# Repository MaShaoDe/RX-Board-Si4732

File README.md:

# RX-Board Si4732

Steckbare Empfänger-Baugruppe für das [Funkfüürli](https://github.com/MaShaoDe/Funkfuerli), das Notfallradio zum Selberbauen für Kinder und Schüler.

Das RX-Board trägt den Empfängerchip Si4732-A10 (UKW, MW, KW, LW, RDS) mit Quarz und Beschaltung. Es wird komplett bestückt bestellt. Die Kinder löten nur die Stiftleisten.

**Stand:** Rev A ist bestellt, gefertigt und unterwegs. Die Tests folgen nach Lieferung (siehe [docs/labortest.md](docs/labortest.md)). Bekannte Fehler auf Rev A werden in Rev B korrigiert.

* Beschreibung, Pinbelegung und Anforderungen: [docs/rx-board.md](docs/rx-board.md)
* Englische Kurzfassung: [README.en.md](README.en.md)
* Lizenzen: [LICENSE.md](LICENSE.md)

## Ordner

| Ordner | Inhalt |
|---|---|
| `docs/` | Beschreibung, Anforderungen, Prüfanleitung |
| `hardware/` | KiCad Projekt, Fertigungsdaten Rev A (Stückliste, Bestückungsliste) |
| `LICENSES/` | Lizenztexte |

## Plan

1. Erledigt: Schaltplan, Layout und Fertigungsdaten Rev A, Fertigung bei JLCPCB.
2. Offen: Test Rev A (Testprogramm liest Chip aus und stimmt einen Sender ab).
3. Offen: Fehler von Rev A sammeln, Layout Rev B.

Copyright 2026 FerienBSD aka Marcel Sauder. Hardware CERN-OHL-P-2.0, Doku CC-BY-4.0.

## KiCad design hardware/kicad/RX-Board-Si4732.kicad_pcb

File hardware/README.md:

# hardware

Rev A des RX-Boards (UKW, MW, LW). Stand 2026-11-19: **gefertigt, Lieferung und Tests stehen aus.** Entwurfsstand vom 2026-11-15: ERC in KiCad 10: 0 Meldungen. DRC Durchgang 2: 0 Fehler. Die Footprints stammen jetzt aus der echten KiCad-Bibliothek (`tools/fplib.json`). Noch offen: DRC der neuen Version, Antennenpfade im Labortest, JLCPCB-Vorschau.

## Inhalt

| Pfad | Inhalt |
|---|---|
| `kicad/RX-Board-Si4732.kicad_pro` | KiCad-Projekt (erzeugt im KiCad-8-Format, in KiCad 10 geladen und gespeichert) |
| `kicad/RX-Board-Si4732.kicad_sch` | Schaltplan. Verbindungen laufen über gleichnamige Netzbezeichner, nicht über gezeichnete Leitungen |
| `kicad/RX-Board-Si4732.kicad_pcb` | Platine 44 x 30 mm, 2 Lagen, bestückt und verlegt, Masseflächen vorne und hinten |
| `bom/RX-Board_RevA_BOM.csv` | Stückliste des Entwurfs. Die Stückliste mit LCSC-Nummern liegt in `production/` |
| `production/` | Fertigungsdaten Rev A (Stückliste mit LCSC-Nummern, Bestückungsdatei), siehe `production/README.md` |
| `preview/layout-vorschau.png` | Grobe Vorschau des Layouts (kein KiCad-Bild) |
| `tools/` | Python-Skripte, die diese Dateien erzeugen (siehe unten). `fplib.json` enthält die Footprints aus der KiCad-Bibliothek |

## Erste Schritte in KiCad

1. Projekt öffnen. Wenn KiCad nach Symbol- oder Footprint-Bibliotheken fragt, "Aktuelle Einstellungen behalten" wählen. Die Symbole sind im Schaltplan eingebettet.
2. Schaltplan: ERC ausführen. Zu erwarten sind Warnungen zu Power-Pins ohne Treiber (alle Pins sind als passiv gesetzt) und "Pin nicht auf Raster".
3. Platine: Zonen füllen (Taste B), dann DRC ausführen. Zu prüfen: Abstände, Silkscreen über Pads, Textgrössen, Beschriftung auf der Rückseite (gespiegelt).
4. Footprints mit "Aktualisieren aus Schaltplan" gegen die Standardbibliothek abgleichen.
5. Layout durchsehen. Das Verlegen hat ein Skript gemacht (Gitter-Router). Kritisch sind die Antennenpfade (FM, AM), der Quarz und die Lage der Teile zum Ferritstab.
6. Gerber, Bohrdateien und Bestückungsdatei (Position) in KiCad exportieren, im JLCPCB-Viewer Drehung der Bauteile prüfen.

## Erzeugen

```
cd hardware/tools
python3 rxwrite.py      # schreibt kicad/ und bom/
python3 fpextract.py <von KiCad gespeicherte .kicad_pcb>   # nur nötig, um fplib.json aus der Bibliothek zu erneuern
python3 rxcheck.py      # Abstands- und Verbindungsprüfung
python3 rxsyntax.py ../kicad/RX-Board-Si4732.kicad_pcb ../kicad/RX-Board-Si4732.kicad_sch
```

Benötigt Python 3 und numpy. `rxmodel.py` enthält Bauteile, Netze und Platzierung. Änderungen dort ergeben nach `rxwrite.py` neue Dateien. Manuelle Änderungen in KiCad werden dabei überschrieben.

## Offen

* Quarz: Bauform 3215, Lastkapazität 12.5 pF, Toleranz laut AN383 ±50 ppm. Der bestellte Typ (LCSC C32346) ist gegen diese Werte zu prüfen.
* FM-Spule 56 nH ist ein Startwert aus AN383 und wird im Labortest geprüft (Mikroe nutzt 270 nH).
* Footprint der Stiftleiste, Kodierung und mechanische Lage zur Hauptplatine festlegen.

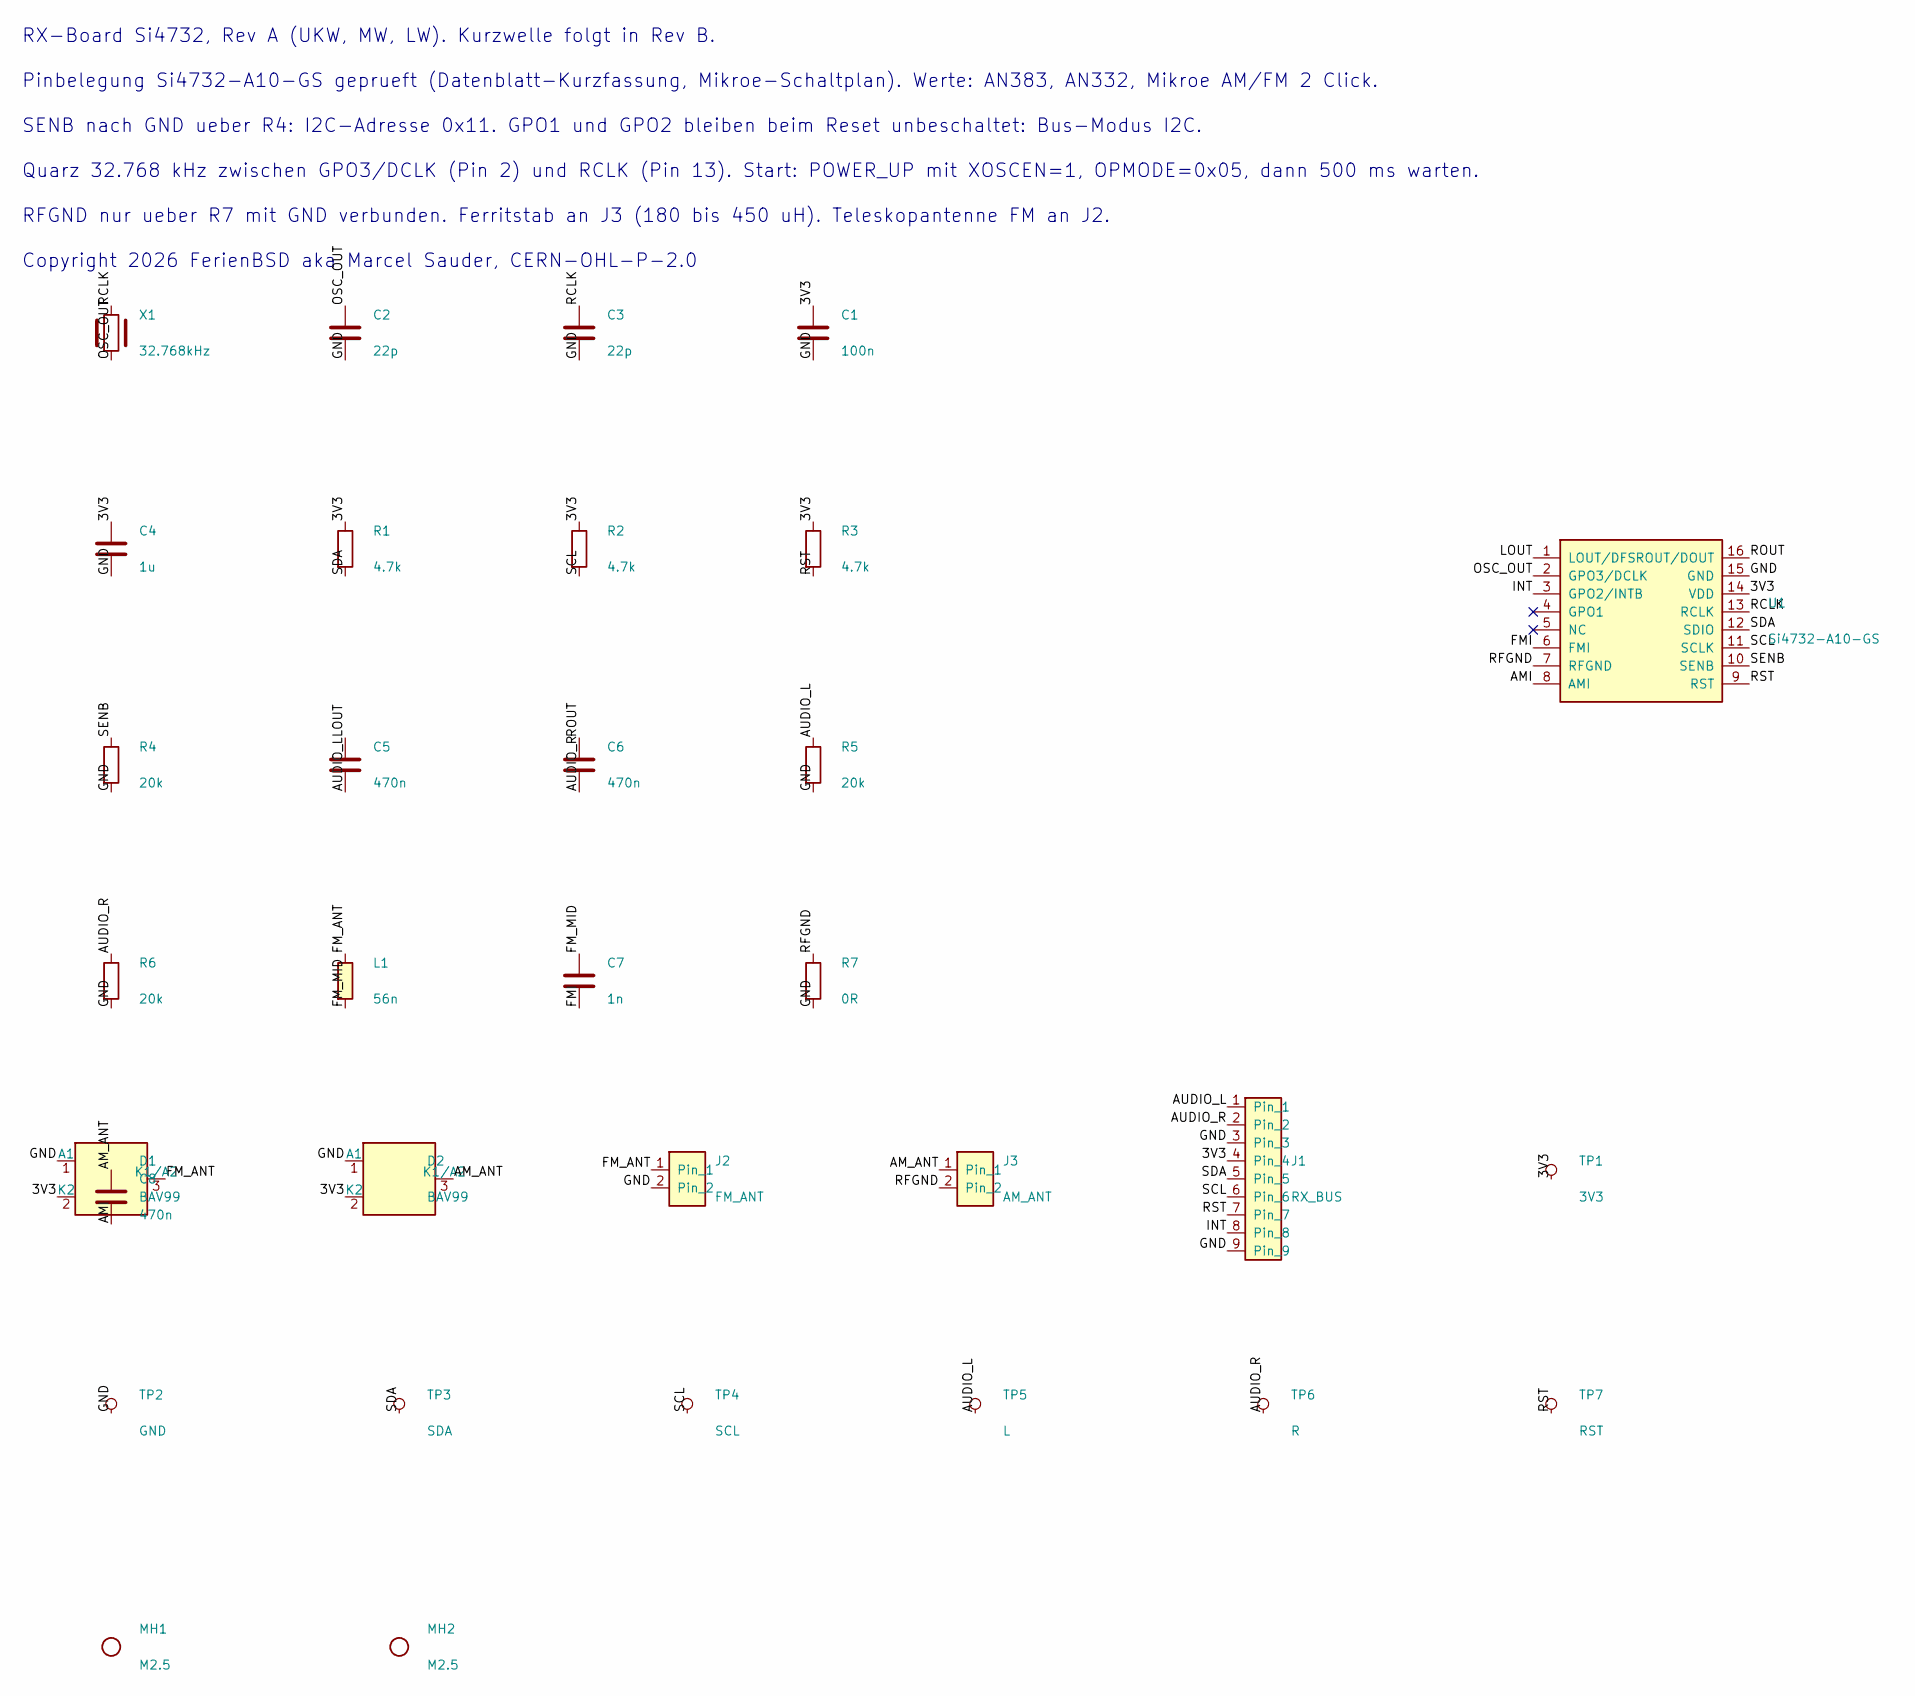
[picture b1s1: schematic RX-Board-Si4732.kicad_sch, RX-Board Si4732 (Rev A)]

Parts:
C1: 100n; C_0805_2012Metric
C2, C3: 22p; C_0805_2012Metric
C4: 1u; C_0805_2012Metric
C5, C6, C8: 470n; C_0805_2012Metric
C7: 1n; C_0805_2012Metric
D1, D2: BAV99; SOT-23
J1: RX_BUS; PinHeader_1x09_P2.54mm_Vertical
J2: FM_ANT; PinHeader_1x02_P2.54mm_Vertical
J3: AM_ANT; PinHeader_1x02_P2.54mm_Vertical
L1: 56n; L_0805_2012Metric
MH1, MH2: M2.5; MountingHole_2.7mm_M2.5
R1, R2, R3: 4.7k; R_0805_2012Metric
R4, R5, R6: 20k; R_0805_2012Metric
R7: 0R; R_0805_2012Metric
TP1: 3V3; TestPoint_Pad_D1.5mm
TP2: GND; TestPoint_Pad_D1.5mm
TP3: SDA; TestPoint_Pad_D1.5mm
TP4: SCL; TestPoint_Pad_D1.5mm
TP5: L; TestPoint_Pad_D1.5mm
TP6: R; TestPoint_Pad_D1.5mm
TP7: RST; TestPoint_Pad_D1.5mm
U1: Si4732-A10-GS; SOIC-16_3.9x9.9mm_P1.27mm
X1: 32.768kHz; Crystal_SMD_3215-2Pin_3.2x1.5mm

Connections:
3V3: C1.1, C4.1, D1.2 (K2), D2.2 (K2), J1.4, R1.1, R2.1, R3.1, TP1.1, U1.14 (VDD)
AMI: C8.2, U1.8 (AMI)
AM_ANT: C8.1, D2.3 (K1/A2), J3.1
AUDIO_L: C5.2, J1.1, R5.1, TP5.1
AUDIO_R: C6.2, J1.2, R6.1, TP6.1
FMI: C7.2, U1.6 (FMI)
FM_ANT: D1.3 (K1/A2), J2.1, L1.1
FM_MID: C7.1, L1.2
GND: C1.2, C2.2, C3.2, C4.2, D1.1 (A1), D2.1 (A1), J1.3, J1.9, J2.2, R4.2, R5.2, R6.2, R7.2, TP2.1, U1.15 (GND)
INT: J1.8, U1.3 (GPO2/INTB)
LOUT: C5.1, U1.1 (LOUT/DFS)
OSC_OUT: C2.1, U1.2 (GPO3/DCLK), X1.2
RCLK: C3.1, U1.13 (RCLK), X1.1
RFGND: J3.2, R7.1, U1.7 (RFGND)
ROUT: C6.1, U1.16 (ROUT/DOUT)
RST: J1.7, R3.2, TP7.1, U1.9 (RST)
SCL: J1.6, R2.2, TP4.1, U1.11 (SCLK)
SDA: J1.5, R1.2, TP3.1, U1.12 (SDIO)
SENB: R4.1, U1.10 (SENB)

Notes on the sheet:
RX-Board Si4732, Rev A (UKW, MW, LW). Kurzwelle folgt in Rev B.
Pinbelegung Si4732-A10-GS geprueft (Datenblatt-Kurzfassung, Mikroe-Schaltplan). Werte: AN383, AN332, Mikroe AM/FM 2 Click.
SENB nach GND ueber R4: I2C-Adresse 0x11. GPO1 und GPO2 bleiben beim Reset unbeschaltet: Bus-Modus I2C.
Quarz 32.768 kHz zwischen GPO3/DCLK (Pin 2) und RCLK (Pin 13). Start: POWER_UP mit XOSCEN=1, OPMODE=0x05, dann 500 ms warten.
RFGND nur ueber R7 mit GND verbunden. Ferritstab an J3 (180 bis 450 uH). Teleskopantenne FM an J2.
Copyright 2026 FerienBSD aka Marcel Sauder, CERN-OHL-P-2.0

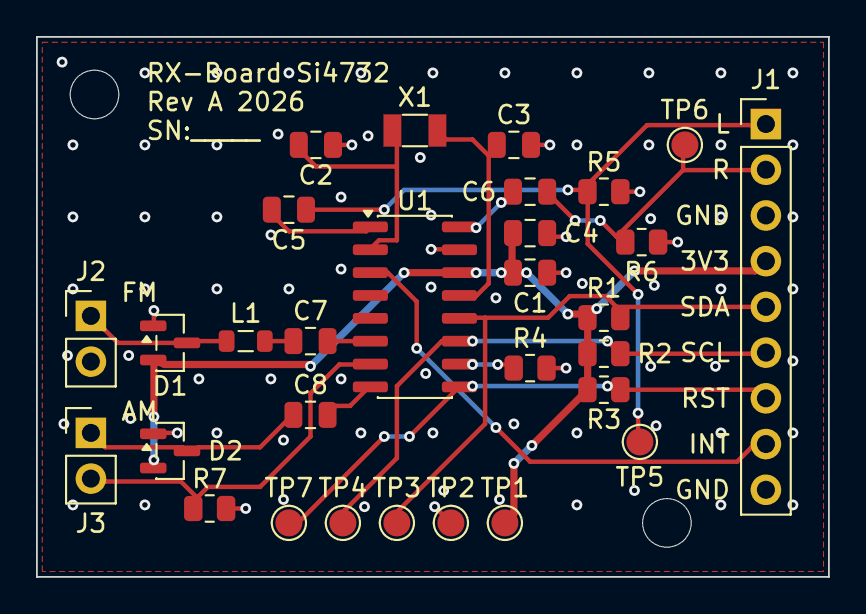
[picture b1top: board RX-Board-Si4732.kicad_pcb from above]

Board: 2 copper layers, 44.0 x 30.0 mm, 32 parts (0 on the bottom side), 19 nets.

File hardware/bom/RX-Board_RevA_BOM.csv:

Comment,Designator,Footprint,LCSC Part #,Beschreibung,Bestueckung
100n,C1,C_0805_2012Metric,C49678,Kondensator X7R 100 nF,ja
22p,"C2,C3",C_0805_2012Metric,C1804,Kondensator C0G 22 pF,ja
1u,C4,C_0805_2012Metric,C49326705,Kondensator X7R 1 uF,ja
470n,"C5,C6,C8",C_0805_2012Metric,C106846,Kondensator X7R 470 nF,ja
1n,C7,C_0805_2012Metric,,Kondensator C0G 1 nF,ja
BAV99,"D1,D2",SOT-23,C68983,Doppeldiode BAV99 (ESD-Schutz),ja
RX_BUS,J1,PinHeader_1x09_P2.54mm_Vertical,,"Stiftleiste 1x9, 2.54 mm","nein, Kinder loeten"
FM_ANT,J2,PinHeader_1x02_P2.54mm_Vertical,,"Stiftleiste 1x2, 2.54 mm","nein, Kinder loeten"
AM_ANT,J3,PinHeader_1x02_P2.54mm_Vertical,,"Stiftleiste 1x2, 2.54 mm","nein, Kinder loeten"
56n,L1,L_0805_2012Metric,C373725,"Induktivitaet 56 nH, Q>=60 bei 200 MHz",ja
4.7k,"R1,R2,R3",R_0805_2012Metric,C17673,Widerstand 4.7 kOhm,ja
20k,"R4,R5,R6",R_0805_2012Metric,C2912590,Widerstand 20 kOhm,ja
0R,R7,R_0805_2012Metric,C17477,Widerstand 0 Ohm,ja
Si4732-A10-GS,U1,SOIC-16_3.9x9.9mm_P1.27mm,C2155558,AM/FM/SW/LW/RDS Empfaenger,ja
32.768kHz,X1,Crystal_SMD_3215-2Pin_3.2x1.5mm,C32346,"Quarz 32.768 kHz, 3.2x1.5 mm, CL 12.5 pF",ja
